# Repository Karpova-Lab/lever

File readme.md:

# Retractable Lever

This repository contains design files for a retractable lever used in behavioral neuroscience experiments.

Full documentation can be found at https://karpova-lab.github.io/lever/

Feedback and questions can be submitted to [discussions](https://github.com/Karpova-Lab/lever/discussions).

## License
This project is licensed under the [Janelia open-source hardware license](license_hardare.txt) and [Janelia 3-term BSD open-source software license](license_software.txt).

Please contact [innovation@janelia.hhmi.org](mailto:innovation@janelia.hhmi.org) if you have any questions about licensing or would like to use this project commercially.

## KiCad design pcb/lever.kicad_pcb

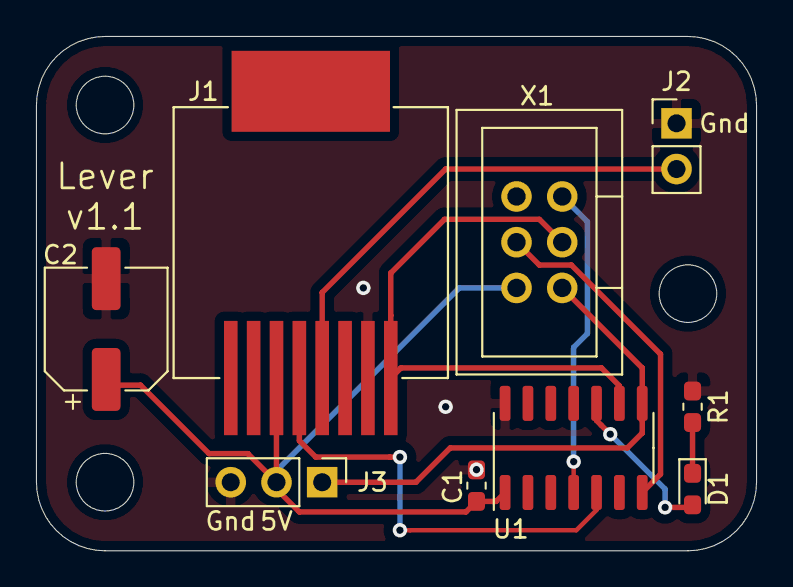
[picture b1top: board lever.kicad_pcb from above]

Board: 2 copper layers, 40.0 x 28.6 mm, 12 parts (0 on the bottom side), 10 nets.

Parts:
C1: 0.1µF; C_0603_1608Metric_Pad1.05x0.95mm_HandSolder
C2: 470 µF; CP_Elec_6.3x4.9
D1: LED; LED_0603_1608Metric_Pad1.05x0.95mm_HandSolder
H1, H2, H3: MountingHole; MountingHole_3.2mm_M3
J1: RJ45_pyControl; RJ45_SMD_Vertical
J2: Conn_01x02; PinHeader_1x02_P2.54mm_Vertical
J3: Conn_01x03; PinHeader_1x03_P2.54mm_Vertical
R1: 10KΩ; R_0603_1608Metric_Pad1.05x0.95mm_HandSolder
U1: ATtiny84-20SSU; SOIC-14_3.9x8.7mm_P1.27mm
X1: AVR_ISP

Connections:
/DIO_A: J1.1, U1.9, X1.3
/DIO_B: J1.4, J2.2
/DIO_C: J1.5, U1.5
/GND: C1.1, C2.2, J1.2, J2.1, J3.3, R1.1, U1.14, X1.6
/Vcc: C1.2, C2.1, J1.6, J3.2, U1.1, X1.2
unnamed: D1.1, R1.2
unnamed: D1.2, U1.10
unnamed: J3.1, U1.8, X1.1
unnamed: U1.4, X1.5
unnamed: U1.7, X1.4

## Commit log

2020-01-21 pcb v1.0
2020-01-21 pcb v1.1
2020-02-04 software initial commit
2020-02-04 can adjust servo position by receiving signal on pyControl's DIO_C. configuration is loaded from and saved to EEPROM
2020-02-18 retracted position is automatically offset by 700, updated when extended position is updated
2020-09-09 PCB bom and rendering updates
2020-09-09 Added 3D and 2D CAD
2020-09-09 Added rough draft of docs
2021-05-25 hugo docs rough draft
2021-05-29 CAD and software updates
2021-05-29 updated docs
2021-06-08 doc updates
2021-06-15 fixed some typos
2021-06-15 update doc theme to latest
2022-06-06 convert documentation from hugo to mkdocs
2022-06-06 lever device file download fix?
2022-06-06 lever_device.py download
2022-06-07 added license and readme
2022-06-07 remove hugo theme submodule
2022-06-07 added PCB layout and schematic
2022-06-10 improved page navigation discoverability
2022-06-10 fixed chapter text getting cutoff
2025-09-05 license updates
2025-11-11 add demo gif to readme
2025-11-25 hardware license update
